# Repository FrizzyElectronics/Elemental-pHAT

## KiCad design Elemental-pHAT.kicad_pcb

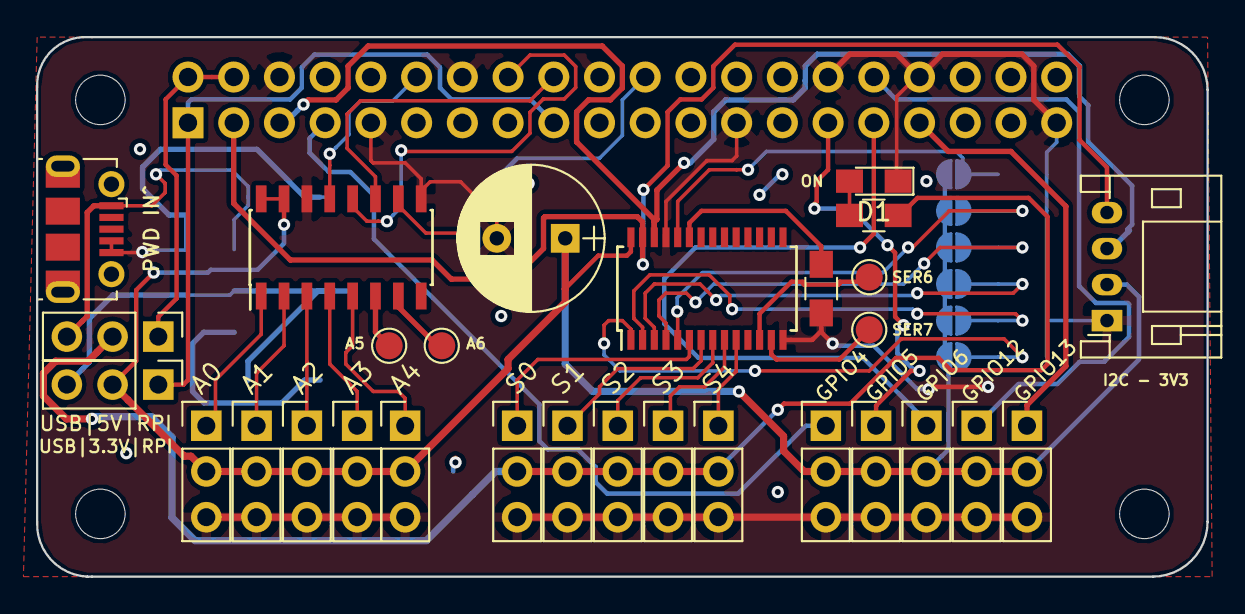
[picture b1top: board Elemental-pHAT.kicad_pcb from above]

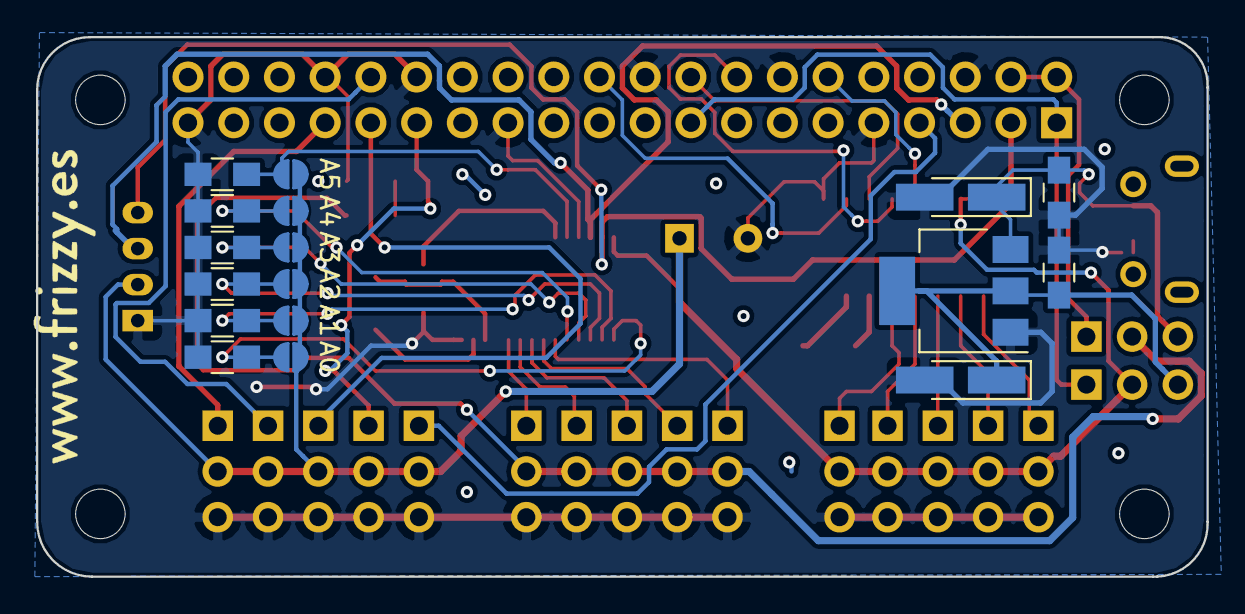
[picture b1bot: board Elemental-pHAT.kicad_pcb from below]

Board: 2 copper layers, 65.0 x 30.0 mm, 47 parts (17 on the bottom side), 40 nets.

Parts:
A0: A0; JUMPER-SOLDER-SMD
A1: A1; JUMPER-SOLDER-SMD
A2: A2; JUMPER-SOLDER-SMD
A3: A3; JUMPER-SOLDER-SMD
A4: A4; JUMPER-SOLDER-SMD
A5: A5; JUMPER-SOLDER-SMD
C1, C4: 22uF; CP_Tantalum_Case-A_EIA-3216-18_Hand
C2, C3: 100nF; C_0805_HandSoldering
C5: 10uF; CP_Radial_D8.0mm_P3.80mm
D1: LED_PURPLE; LED_0805_HandSoldering
I2C: I2C-1; JST_PH_S4B-PH-K_04x2.00mm_Angled
J1: GPIO4; Pin_Header_Straight_1x03_Pitch2.54mm
J2: S0; Pin_Header_Straight_1x03_Pitch2.54mm
J3: A0; Pin_Header_Straight_1x03_Pitch2.54mm
J4: GPIO5; Pin_Header_Straight_1x03_Pitch2.54mm
J5: S1; Pin_Header_Straight_1x03_Pitch2.54mm
J6: A1; Pin_Header_Straight_1x03_Pitch2.54mm
J7: GPIO6; Pin_Header_Straight_1x03_Pitch2.54mm
J8: S2; Pin_Header_Straight_1x03_Pitch2.54mm
J9: A2; Pin_Header_Straight_1x03_Pitch2.54mm
J10: USB; USB_Micro-B_Molex-105017-0001
J11: GPIO12; Pin_Header_Straight_1x03_Pitch2.54mm
J12: S3; Pin_Header_Straight_1x03_Pitch2.54mm
J13: A3; Pin_Header_Straight_1x03_Pitch2.54mm
J14: JP_3.3V; Pin_Header_Straight_1x03_Pitch2.54mm
J15: GPIO13; Pin_Header_Straight_1x03_Pitch2.54mm
J16: S4; Pin_Header_Straight_1x03_Pitch2.54mm
J17: A4; Pin_Header_Straight_1x03_Pitch2.54mm
J18: CH5; Test_Point_Pad_d1.5mm
J19: CH6; Test_Point_Pad_d1.5mm
J21: JP_5V; Pin_Header_Straight_1x03_Pitch2.54mm
J24: SER6; Test_Point_Pad_d1.5mm
J25: SER7; Test_Point_Pad_d1.5mm
R1: 1k; R_0805_HandSoldering
R2, R3, R4, R5, R6, R7, R8: 10k; R_0805_HandSoldering
U1: Rpi3_Header; z_RPiZero_Hat_NPTH
U2: AMS1117; SOT-223
U3: PCA9685; TSSOP-28_4.4x9.7mm_Pitch0.65mm
U4: MCP3008; SOIC-16_3.9x9.9mm_Pitch1.27mm

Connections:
+3V3: A0.1, A1.1, A2.1, A3.1, A4.1, A5.1, C5.1, I2C.2, J1.2, J3.2, J4.2, J6.2, J7.2, J9.2, J11.2, J13.2, J14.2, J15.2, J17.2, U3.28, U4.15, U4.16
+5V: J2.2, J5.2, J8.2, J12.2, J16.2, J21.2, R1.1
/3V3RPI: J14.1, U1.1, U1.17
/3V3USB: C3.1, C4.1, J14.3, U2.2, U2.4
/5VRPI: J21.1, U1.2, U1.4
/5VUSB: C1.1, C2.1, J10.1, J21.3, U2.3
/A0: A0.2, R2.1, U3.1
/A1: A1.2, R3.1, U3.2
/A2: A2.2, R4.1, U3.3
/A3: A3.2, R5.1, U3.4
/A4: A4.2, R6.1, U3.5
/A5: A5.2, R7.1, U3.24
/CH0: J3.1, U4.1
/CH1: J6.1, U4.2
/CH2: J9.1, U4.3
/CH3: J13.1, U4.4
/CH4: J17.1, U4.5
/CH5: J18.1, U4.6
/CH6: J19.1, U4.7
/CLK: U1.12, U4.13
/CS: U1.22, U4.10
/Din: U1.18, U4.11
/Dout: U1.16, U4.12
/GPIO4: J1.1, U1.7
/GPIO5: J4.1, U1.29
/GPIO6: J7.1, U1.31
/GPIO12: J11.1, U1.32
/GPIO13: J15.1, U1.33
/SCL: I2C.3, U1.5, U3.26
/SDA: I2C.4, U1.3, U3.27
/SER0: J2.1, U3.6
/SER1: J5.1, U3.7
/SER2: J8.1, U3.8
/SER3: J12.1, U3.9
/SER4: J16.1, U3.10
/SER6: J24.1, U3.12
/SER7: J25.1, U3.13
GND: C1.2, C2.2, C3.2, C4.2, C5.2, D1.1, I2C.1, J1.3, J2.3, J3.3, J4.3, J5.3, J6.3, J7.3, J8.3, J9.3, J10.4, J10.5, J11.3, J12.3, J13.3, J15.3, J16.3, J17.3, R2.2, R3.2, R4.2, R5.2, R6.2, R7.2, R8.2, U1.6, U1.9, U1.14, U1.20, U1.25, U1.30, U1.34, U1.39, U2.1, U3.14, U3.25, U4.9, U4.14
unnamed: D1.2, R1.2
unnamed: R8.1, U3.23

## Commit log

2018-06-18 Primeros componenetes añadidos
2018-06-25 conectores añadidos
2018-06-25 Jumpers añadidos
2018-06-25 Nombres puestos
2018-07-07 Esquema terminado
2018-07-07 CVPCB y netlist finished
2018-07-08 Extra pads deleted
2018-07-08 Routed
2018-07-08 Silkscreen finished
2018-07-08 Cam Files Exported
